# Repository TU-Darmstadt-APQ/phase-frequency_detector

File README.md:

Phase-Frequency Detector
=====================
This repository contains the [KiCad](https://www.kicad.org/) design files of a phase-frequency detector designed for application in optical phase-locked loops (OPLL). The detector compares a beat-note signal with a reference signal and creates an output signal proportional to the phase deviation of the beat-note from the reference. Optionally, the beat-note input can be equipped with a divider (default: 4) for a larger input-frequency range.  The module also comprises a fast analog proportional-derivative controller for high-bandwidth feedback. 

**Features**

- Input frequency range
  - 10 MHz to 1.3 GHz without divider
  - 500 MHz to 5.2 GHz with divider (HMC365)
- Input signal level: -10 dBm to +10 dBm
- Error signal output:
  - Bandwidth 4 MHz (2. order filter)
  - Output voltage ±1 V max. (high-Z)
- PD controller
  - Output voltage ±5 V max. (high-Z)
  - Level adjustable between 4% and 100% via frontpanel trim pot
  - Gain sign adjustable via frontpanel switch
  - Hardware adjustable corner-frequency (default: 0.8 MHz) and gain limit (default: 32 dB)

Assembly
---------------

The PCB is placed in a standard 19''-rack mount unit. Use the [switch breakout board](https://github.com/TU-Darmstadt-APQ/phase-frequency_detector_switch_breakout) for connecting the frontpanel switch of the PD controller. See `frontpanel/` folder for drawings and frontpanel artwork.

 Design Files
-------------------
The design files can be found on the [releases](../../releases) page and include the following resources:

- Schematics as a PDF
- Gerber files
- Pick & place position files
- Bill of materials as a CSV file and also as an interactive HTML version

The latest revision of those files can be found [here](../../releases/latest).

Related work
--------------------
T. Preuschoff, *Laser Technologies for Applications in Quantum Information Science*, Ph.D. thesis, TU Darmstadt, 2023, [https://tuprints.ulb.tu-darmstadt.de/23242/](https://tuprints.ulb.tu-darmstadt.de/23242/)

Requirements
----------------------
- Dual power supply
   - +15 V (0.35 A typ.)
   - \- 15 V (0.15 A typ.)
- 19-inch rack mount (e.g. [Fischer Elektronik BGT384](https://www.fischerelektronik.de/web_fischer/en_GB/cases/N05.1/19%22%20subracks/$catalogue/fischerData/PR/BGT384_180/search.xhtml))

License
-----------

This work is released under the CERN OHL v.1.2
See www.ohwr.org/licenses/cern-ohl/v1.2 or the included LICENSE file for more information.

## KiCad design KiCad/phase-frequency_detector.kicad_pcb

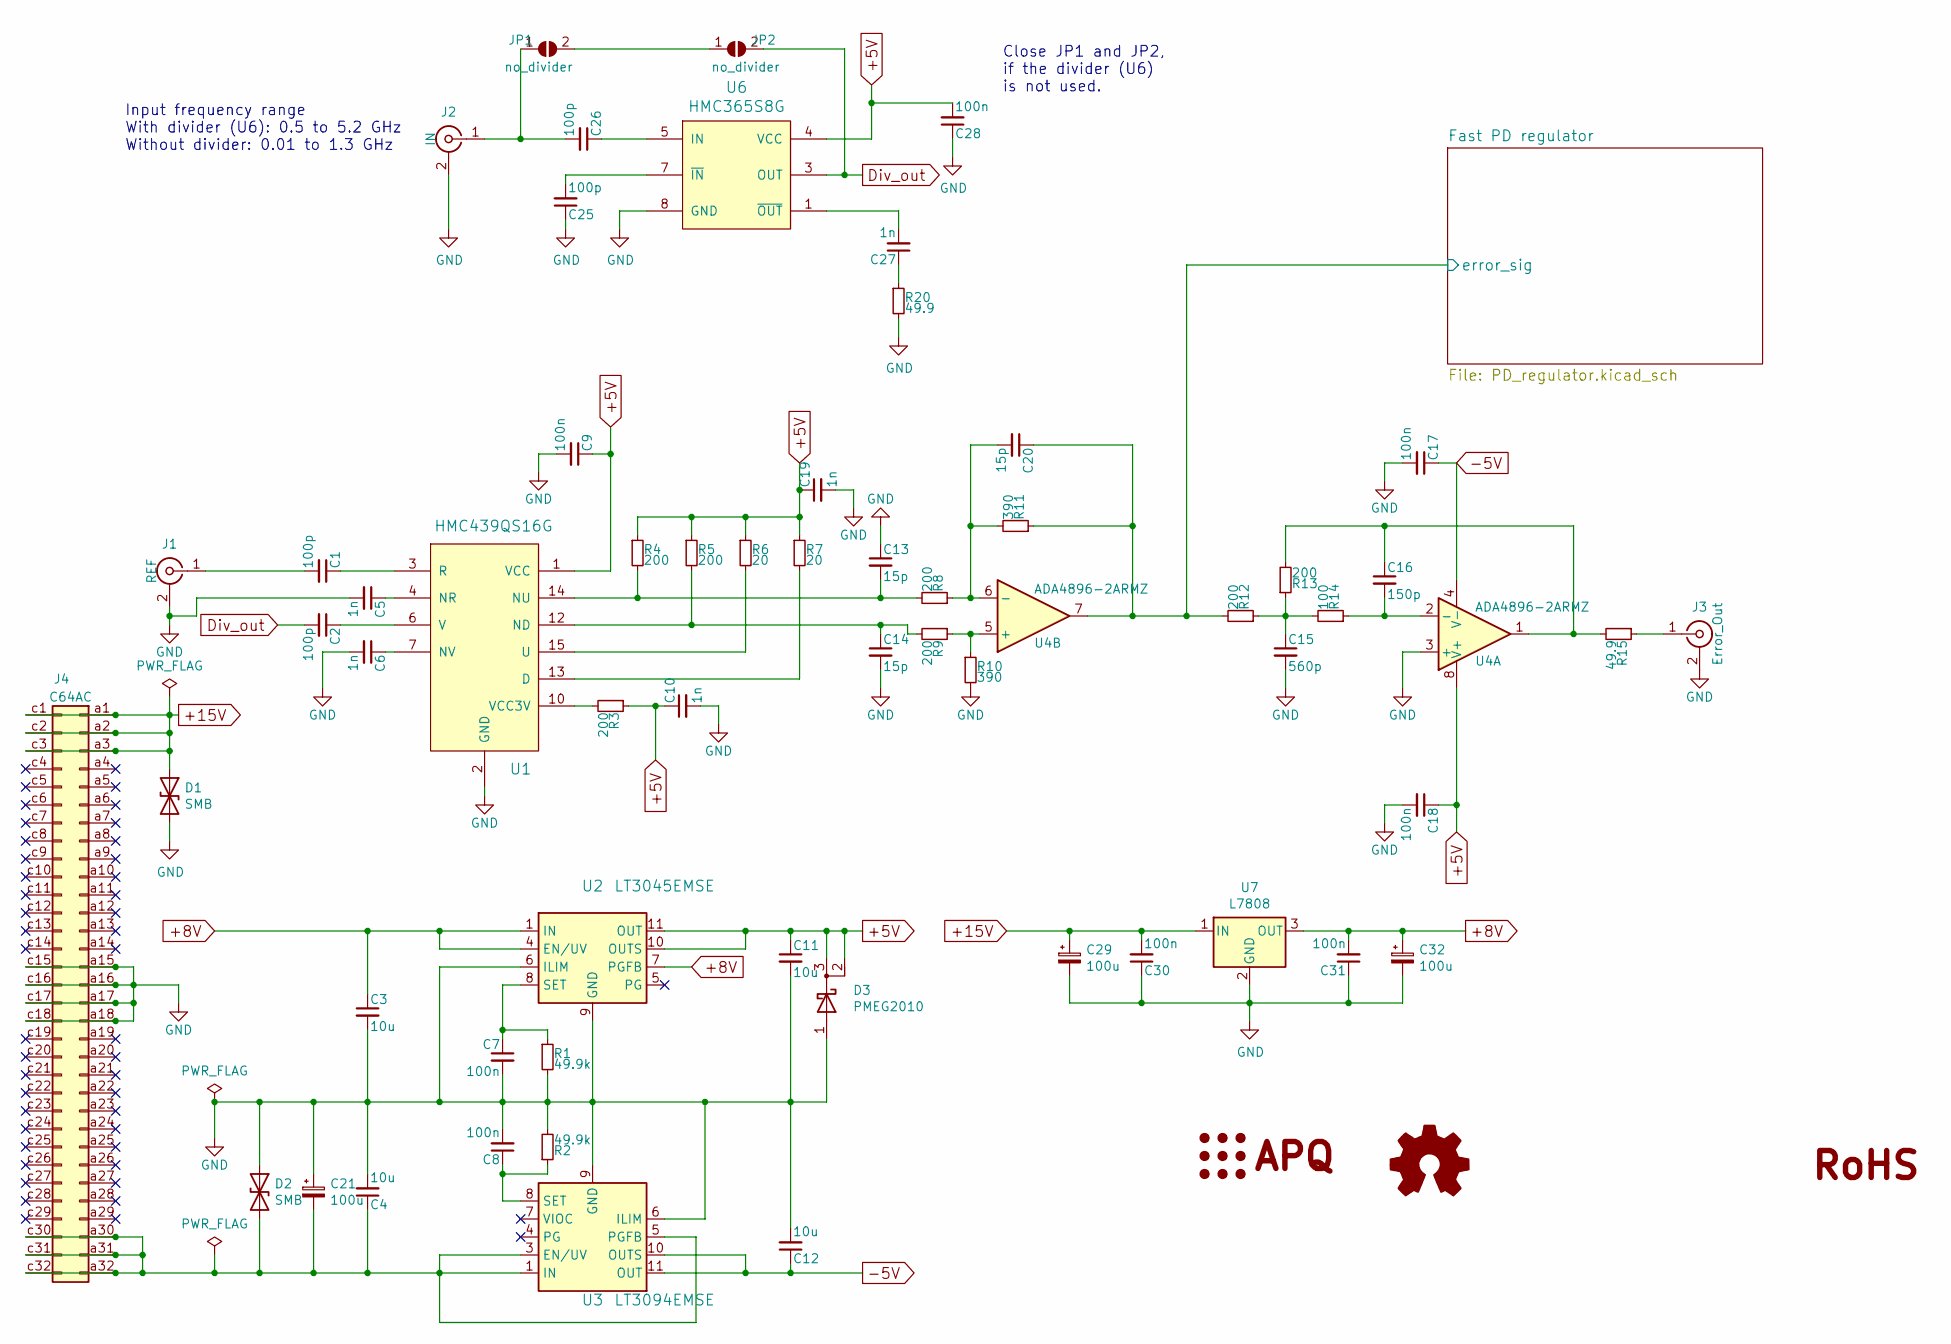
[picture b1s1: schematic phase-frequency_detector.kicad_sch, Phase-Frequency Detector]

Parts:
C1, C2, C25, C26: 100p; C_0603_1608Metric
C3, C4, C11, C12: 10u; C_1210_3225Metric
C5, C6, C10, C19, C27: 1n; C_0603_1608Metric
C7, C8: 100n; C_1206_3216Metric
C9, C17, C18, C28, C30, C31: 100n; C_0603_1608Metric
C13, C14, C20: 15p; C_0603_1608Metric
C15: 560p; C_0603_1608Metric
C16: 150p; C_0603_1608Metric
C21, C29, C32: 100u; CP_Radial_D5.0mm_P2.50mm
D1, D2: SMB; D_SMB
D3: PMEG2010; SOT-23
J1: REF; SMA_Amphenol_132289_EdgeMount
J2: IN; SMA_Amphenol_132289_EdgeMount
J3: Error_Out; BNC_Amphenol_B6252HB-NPP3G-50_Horizontal
J4: C64AC; DIN41612_C_2x32_Male_Horizontal_THT
JP1, JP2: no_divider; SolderJumper-2_P1.3mm_Open_RoundedPad1.0x1.5mm
LOGO1: Logo_APQ; APQ-Logo
LOGO2: Logo_Open_Hardware_Small; OSHW-Logo_5.7x6mm_SilkScreen
LOGO3: Logo_ROHS; RoHS-Logo_6mm_SilkScreen
R1, R2: 49.9k; R_0603_1608Metric
R3, R4, R5, R8, R9, R12, R13: 200; R_0603_1608Metric
R6, R7: 20; R_0603_1608Metric
R10, R11: 390; R_0603_1608Metric
R14: 100; R_0603_1608Metric
R15: 49.9; R_1210_3225Metric
R20: 49.9; R_0603_1608Metric
U1: HMC439QS16G; QSOP-16_3.9x4.9mm_P0.635mm_EP_2.3mmx1.75mm_DNF
U2: LT3045EMSE; MSOP-12-1EP_3x4mm_P0.65mm_EP1.65x2.85mm
U3: LT3094EMSE; MSOP-12-1EP_3x4mm_P0.65mm_EP1.65x2.85mm
U4: ADA4896-2ARMZ; MSOP-8_3x3mm_P0.65mm_mod
U6: HMC365S8G; SOIC-8-1EP_3.9x4.9mm_P1.27mm_EP2.41x3.81mm
U7: L7808; TO-220-3_Vertical

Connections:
+5V: C9.1, C10.1, C11.1, C18.1, C19.1, C28.2, D3.2 (K), D3.3 (K), R3.1, R4.1, R5.1, R6.1, R7.1, U1.1 (VCC), U2.10 (OUTS), U2.11 (OUT), U2.12 (OUT), U4.8 (V+), U6.4 (VCC); also elsewhere on the board
+8V: C3.1, C31.2, C32.1, U2.1 (IN), U2.2 (IN), U2.3 (IN), U2.4 (EN/UV), U2.7 (PGFB), U7.3 (OUT)
+15V: C29.1, C30.2, D1.1 (A1), J4.a1, J4.a2, J4.a3, J4.c1, J4.c2, J4.c3, U7.1 (IN)
-5V: C12.1, C17.1, U3.10 (OUTS), U3.11 (OUT), U3.12 (OUT), U4.4 (V-); also elsewhere on the board
/Fast PD regulator/error_sig: C20.1, R11.1, R12.2, U4.7; also elsewhere on the board
Div_out: C2.2, JP2.2 (B), U6.3 (OUT)
GND: C3.2, C4.2, C5.2, C6.2, C7.2, C8.2, C9.2, C10.2, C11.2, C12.2, C13.1, C14.2, C15.2, C17.2, C18.2, C19.2, C21.1, C25.1, C28.1, C29.2, C30.1, C31.1, C32.2, D1.2 (A2), D2.1 (A1), D3.1 (A), J1.2 (Ext), J2.2 (Ext), J3.2 (Ext), J4.a15, J4.a16, J4.a17, J4.a18, J4.c15, J4.c16, J4.c17, J4.c18, R1.2, R2.2, R10.2, R20.2, U1.2 (GND), U1.5 (GND), U1.8 (GND), U1.9 (GND), U1.11 (GND), U1.16 (GND), U1.17 (GND), U2.6 (ILIM), U2.9 (GND), U2.13 (GND), U3.6 (ILIM), U3.9 (GND), U4.3 (+), U6.8 (GND), U6.9 (GND), U7.2 (GND); also elsewhere on the board
unnamed: C15.1, R12.1, R13.1, R14.2
unnamed: C16.1, R13.2, R15.2, U4.1
unnamed: C27.1, R20.1
unnamed: C4.1, C21.2, D2.2 (A2), J4.a30, J4.a31, J4.a32, J4.c30, J4.c31, J4.c32, U3.1 (IN), U3.2 (IN), U3.3 (EN/UV), U3.5 (PGFB), U3.13 (IN)
unnamed: C1.2, J1.1 (In)
unnamed: C26.2, J2.1 (In), JP1.1 (A)
unnamed: J3.1 (In), R15.1
unnamed: JP1.2 (B), JP2.1 (A)
unnamed: R7.2, U1.13 (D)
unnamed: C14.1, R5.2, R9.2, U1.12 (ND)
unnamed: C5.1, U1.4 (NR)
unnamed: C13.2, R4.2, R8.2, U1.14 (NU)
unnamed: C6.1, U1.7 (NV)
unnamed: C1.1, U1.3 (R)
unnamed: R6.2, U1.15 (U)
unnamed: C2.1, U1.6 (V)
unnamed: R3.2, U1.10 (VCC3V)
unnamed: C7.1, R1.1, U2.8 (SET)
unnamed: C8.1, R2.1, U3.8 (SET)
unnamed: C16.2, R14.1, U4.2 (-)
unnamed: R9.1, R10.1, U4.5 (+)
unnamed: C20.2, R8.1, R11.2, U4.6 (-)
unnamed: C26.1, U6.5 (IN)
unnamed: C25.2, U6.7 (~IN)
unnamed: C27.2, U6.1 (~OUT)

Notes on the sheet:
Input frequency range With divider (U6): 0.5 to 5.2 GHz Without divider: 0.01 to 1.3 GHz
Close JP1 and JP2, if the divider (U6) is not used.

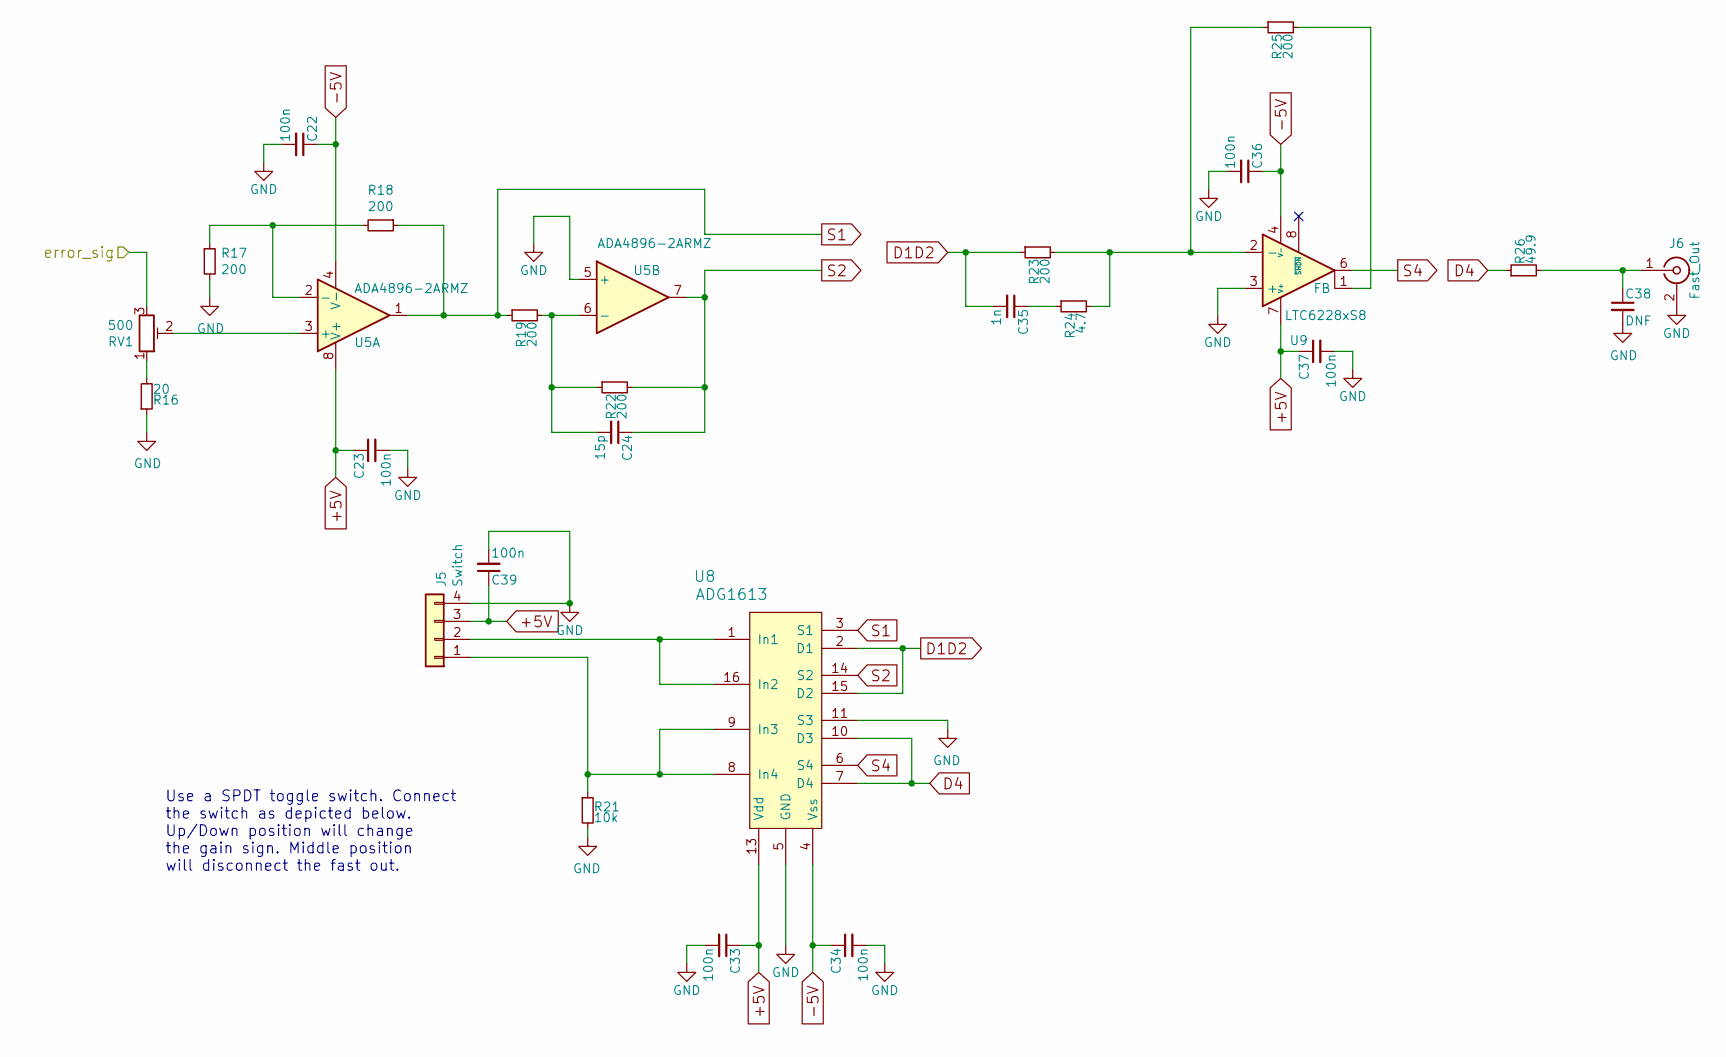
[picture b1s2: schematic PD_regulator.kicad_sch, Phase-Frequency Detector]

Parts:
C22, C23, C33, C34, C36, C37, C39: 100n; C_0603_1608Metric
C24: 15p; C_0603_1608Metric
C35: 1n; C_0603_1608Metric
C38: DNF; C_0603_1608Metric
J5: Switch; JST_PH_B4B-PH-K_1x04_P2.00mm_Vertical
J6: Fast_Out; BNC_Amphenol_B6252HB-NPP3G-50_Horizontal
R16: 20; R_0603_1608Metric
R17, R18, R19, R22, R23, R25: 200; R_0603_1608Metric
R21: 10k; R_0603_1608Metric
R24: 4.7; R_0603_1608Metric
R26: 49.9; R_1210_3225Metric
RV1: 500; Potentiometer_Vishay_43_Horizontal
U5: ADA4896-2ARMZ; MSOP-8_3x3mm_P0.65mm_mod
U8: ADG1613; TSSOP-16_4.4x5mm_P0.65mm
U9: LTC6228xS8; SO-8_3.9x4.9mm_P1.27mm

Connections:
+5V: C23.1, C33.1, C37.1, C39.1, J5.3, U5.8 (V+), U8.13 (Vdd), U9.7 (V+); also elsewhere on the board
-5V: C22.1, C34.1, C36.1, U5.4 (V-), U8.4 (Vss), U9.4 (V-), U9.5 (V-); also elsewhere on the board
/Fast PD regulator/error_sig: RV1.3; also elsewhere on the board
D1D2: C35.2, R23.1, U8.2 (D1), U8.15 (D2)
D4: R26.1, U8.7 (D4), U8.10 (D3)
GND: C22.2, C23.2, C33.2, C34.2, C36.2, C37.2, C38.2, C39.2, J5.4, J6.2 (Ext), R16.1, R17.2, R21.2, U5.5 (+), U8.5 (GND), U8.11 (S3), U9.3 (+); also elsewhere on the board
unnamed: C35.1, R24.1
unnamed: J5.1, R21.1, U8.8 (In4), U8.9 (In3)
unnamed: J5.2, U8.1 (In1), U8.16 (In2)
unnamed: C38.1, J6.1 (In), R26.2
unnamed: R16.2, RV1.1
unnamed: RV1.2, U5.3 (+)
unnamed: R17.1, R18.2, U5.2 (-)
unnamed: C24.2, R19.2, R22.1, U5.6 (-)
unnamed: R23.2, R24.2, R25.1, U9.2 (-)
unnamed: R25.2, U9.1 (FB)
S1: R18.1, R19.1, U5.1, U8.3 (S1)
S2: C24.1, R22.2, U5.7, U8.14 (S2)
S4: U8.6 (S4), U9.6

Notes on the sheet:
Use a SPDT toggle switch. Connect the switch as depicted below. Up/Down position will change the gain sign. Middle position will disconnect the fast out.

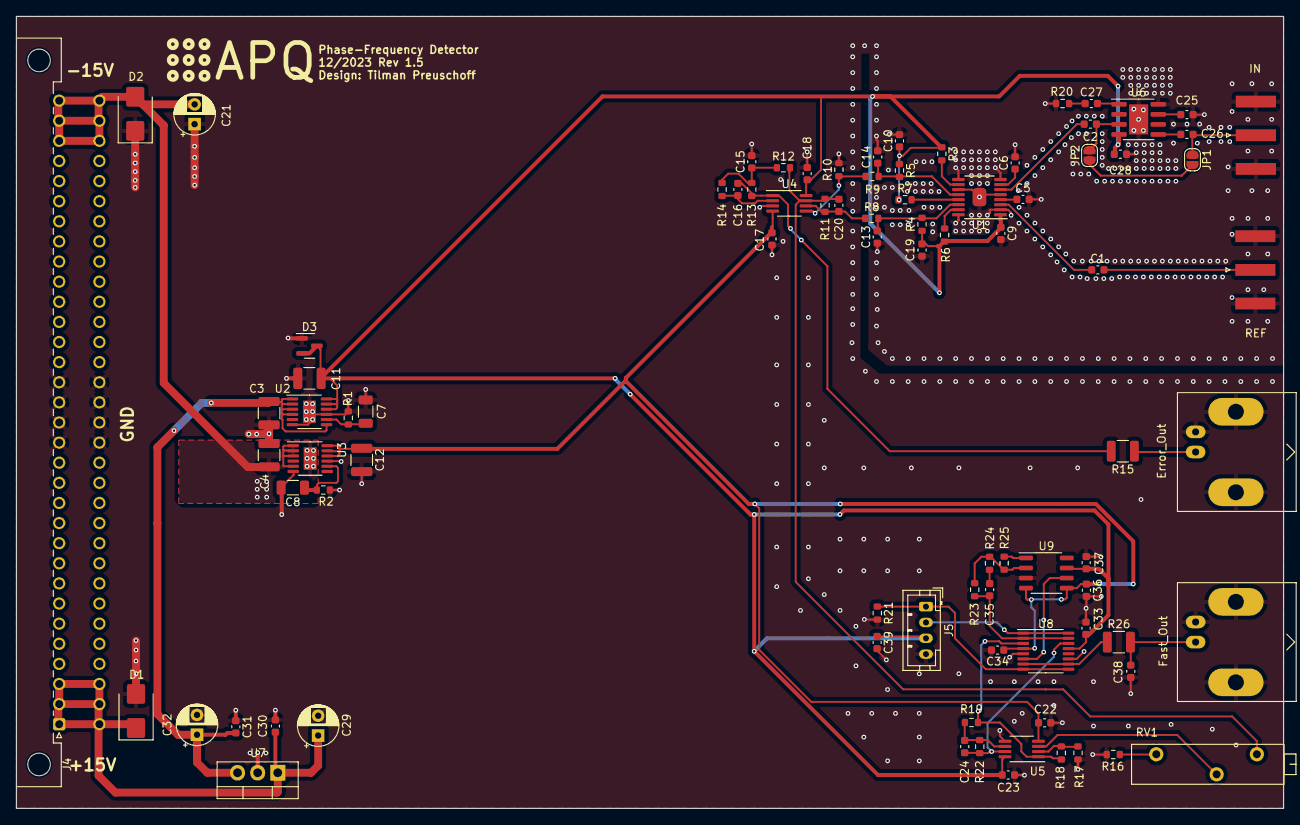
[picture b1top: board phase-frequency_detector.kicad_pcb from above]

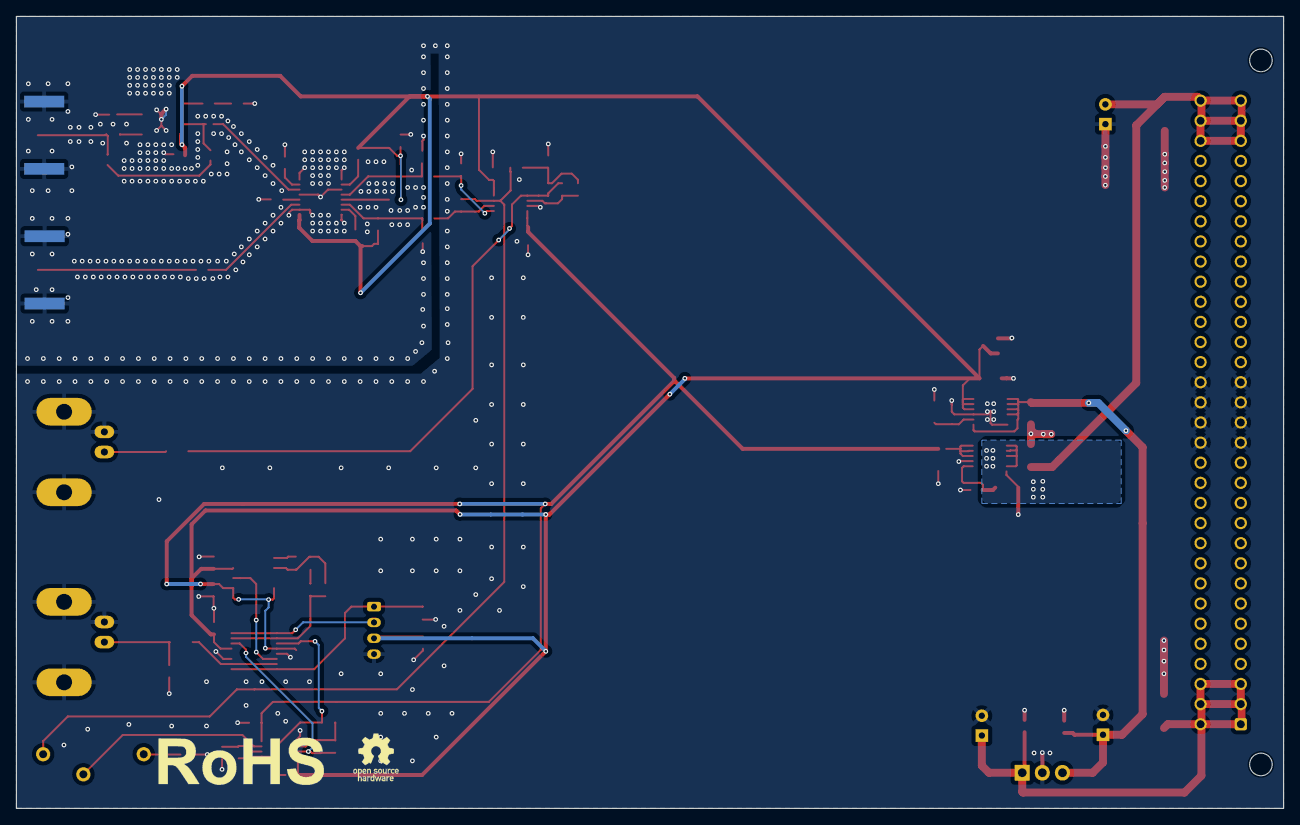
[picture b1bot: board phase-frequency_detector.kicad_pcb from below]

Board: 2 copper layers, 160.0 x 100.0 mm, 89 parts (2 on the bottom side), 47 nets.

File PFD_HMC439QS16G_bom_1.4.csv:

Component,Quantity Per PCB,References,Value,MFN,PN,Description,Footprint,Sheetpath
1,4,C13-C14  C20  C24,15p,Vishay / Vitramon,VJ0603A150JXBAC,"Unpolarized capacitor, small symbol",C_0603_1608Metric,/
2,4,C1-C2  C25-C26,100p,TDK,CGJ3E2C0G2A101J080AA,"Unpolarized capacitor, small symbol",C_0603_1608Metric,/
3,1,C16,150p,Vishay / Vitramon,VJ0603A151JXBAC,"Unpolarized capacitor, small symbol",C_0603_1608Metric,/
4,1,C15,560p,Vishay / Vitramon,VJ0603A561JXAAC,"Unpolarized capacitor, small symbol",C_0603_1608Metric,/
5,6,C5-C6  C10  C19  C27  C35,1n,KEMET,C0603X102K4RACAUTO,"Unpolarized capacitor, small symbol",C_0603_1608Metric,/
6,13,C9  C17-C18  C22-C23  C28  C30-C31  C33-C34  C36-C37  C39,100n,KEMET,C0603C104K5RAC3121,"Unpolarized capacitor, small symbol",C_0603_1608Metric,/
7,2,C7-C8,100n,Murata-Electronics,GRM3195C2A104JA01D,"Unpolarized capacitor, small symbol",C_1206_3216Metric,/
8,4,C3-C4  C11-C12,10u,TDK,C3225X7R2A106K250AC,"Unpolarized capacitor, small symbol",C_1210_3225Metric,/
9,3,C21  C29  C32,100u,Panasonic,ECA-1AM101I,"Polarized capacitor, small symbol",CP_Radial_D5.0mm_P2.50mm,/
10,1,D3,PMEG2010,Nexperia,"PMEG2010AET,215","Schottky diode, cathode on pins 2 and 3",SOT-23,/
11,2,D1-D2,SMB,Bourns,SMBJ40CA-QH,Bidirectional transient-voltage-suppression diode,D_SMB,/
12,1,J4,C64AC,Harting,09221326921222,"DIN41612 connector, double row (AC), 02x32, script generated (kicad-library-utils/schlib/autogen/connector/)",DIN41612_C_2x32_Male_Horizontal_THT,/
13,1,J3,Error_Out,Linx Technologies,CONBNC002,"coaxial connector (BNC, SMA, SMB, SMC, Cinch/RCA, LEMO, ...)",BNC_Amphenol_B6252HB-NPP3G-50_Horizontal,/
14,1,J6,Fast_Out,Linx Technologies,CONREVSMA006.062-G,"coaxial connector (BNC, SMA, SMB, SMC, Cinch/RCA, LEMO, ...)",BNC_Amphenol_B6252HB-NPP3G-50_Horizontal,/Fast PD regulator/
15,2,J1-J2,REF,Linx Technologies,CONREVSMA006.062-G,"coaxial connector (BNC, SMA, SMB, SMC, Cinch/RCA, LEMO, ...)",SMA_Amphenol_132289_EdgeMount,/
16,1,J5,Switch,JST,B4B-PH-K-S,"Generic connector, single row, 01x04, script generated (kicad-library-utils/schlib/autogen/connector/)",JST_PH_B4B-PH-K_1x04_P2.00mm_Vertical,/Fast PD regulator/
17,1,R24,4.7,ROHM Semiconductor,SDR03EZPF4R70,"Resistor, small symbol",R_0603_1608Metric,/Fast PD regulator/
18,3,R6-R7  R16,20,Yageo,AC0603FR-0720RL,"Resistor, small symbol",R_0603_1608Metric,/
19,2,R15  R26,49.9,Vishay / Dale,CRCW121049R9FKEA,"Resistor, small symbol",R_1210_3225Metric,/
20,1,R20,49.9,Panasonic,ERJ-UP3F49R9V,"Resistor, small symbol",R_0603_1608Metric,/
21,1,R14,100,Yageo,RC0603FR-13100RL,"Resistor, small symbol",R_0603_1608Metric,/
22,13,R3-R5  R8-R9  R12-R13  R17-R19  R22-R23  R25,200,Yageo,RC0603FR-13200RL,"Resistor, small symbol",R_0603_1608Metric,/
23,2,R10-R11,390,Yageo,RC0603FR-13390RL,"Resistor, small symbol",R_0603_1608Metric,/
24,1,R21,10k,Panasonic,ERJ-3GEYJ103V,"Resistor, small symbol",R_0603_1608Metric,/Fast PD regulator/
25,2,R1-R2,49.9k,Panasonic,ERJ-UP3F4992V,"Resistor, small symbol",R_0603_1608Metric,/
26,1,RV1,500,Vishay / Spectrol,M43P501KB40,Trim-potentiometer,Potentiometer_Vishay_43_Horizontal,/Fast PD regulator/
27,2,U4-U5,ADA4896-2ARMZ,Analog Devices,ADA4896-2ARMZ,"1 nV/√Hz, Low Power,Rail-to-Rail Output Amplifier",MSOP-8_3x3mm_P0.65mm_mod,/
28,1,U8,ADG1613,Analog Devices,ADG1613BRUZ,,TSSOP-16_4.4x5mm_P0.65mm,/Fast PD regulator/
29,1,U7,L7808,STMicroelectronics,L7808ABV-DG,"Positive 1.5A 35V Linear Regulator, Fixed Output 8V, TO-220/TO-263/TO-252",TO-220-3_Vertical,/
30,1,U2,LT3045EMSE,Analog Devices,LT3045EMSE#PBF,"20V, 500mA, Ultralow Noise, Ultrahigh PSRR Linear Regulator, MSOP Package",MSOP-12-1EP_3x4mm_P0.65mm_EP1.65x2.85mm,/
31,1,U3,LT3094EMSE,Analog Devices,LT3094EMSE#PBF,"–20V, 500mA, Ultralow Noise, Ultrahigh PSRR Negative Linear Regulator, MSOP Package",MSOP-12-1EP_3x4mm_P0.65mm_EP1.65x2.85mm,/
32,1,U9,LTC6228xS8,Analog Devices,LTC6228IS8#PBF,"Low Distortion Rail-to-Rail Output Op Amp with Shutdown, SO-8",SO-8_3.9x4.9mm_P1.27mm,/Fast PD regulator/





Component Groups:,36
Component Count:,86
Fitted Components:,81
Number of PCBs:,1
Total components:,81
Schematic Version:,1.4
Schematic Date:,2022-01-25
PCB Variant:,default
BoM Date:,22.03.2023 21:40:04
Schematic Source:,PFD_HMC439QS16G.kicad_sch
KiCad Version:,Eeschema (6.0.7)

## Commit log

2020-11-23 Rev 1.1
2020-12-04 Reverse Trimpot. Update gerber files
2021-03-18 Rev. 1.2
    -Divide input signal by 4 using HMC365
    -Change board layout to standard eurocard
    -Minor changes to 'Fast Out': Optional AC-coupling, optional gain
2021-03-19 Add gain of 2 and increase bandwidth at U4B
2021-03-19 Add footprint position files
2021-03-21 Update gerber files
2021-08-22 Remove HMC365 frequency divider
2021-08-23 Update revision label on PCB
2021-12-02 Update error signal gains and fix copper pour at LT3094
2021-12-02 Add LM7908 and TVS diodes for line protection
2022-01-17 First draft: fast PD regulator
2022-01-18 Fast PD second draft
2022-01-18 Spice simulations
2022-01-18 Add fast PD regulator
2022-01-18 Add drawing and comment for switch connection
2022-01-24 Add 'no divider' option and clamping diode / Update to KiCad 6
2022-01-25 Fix HMC365 and ADG1413 symbols. Update gerber files.
2022-01-25 Remove additional KiCad 5 gerber files
2022-01-27 Remove KiCad 5 files and ignore backup files
2022-01-27 Update BOM / fix some fottprints
2022-06-09 Updated BOM with new parts
2022-06-13 Update BOM.ini. Generate BOM.
2023-03-22 Update BOM
2023-03-22 Rename project files
2023-03-22 Add comments and fix custom footprint lib.
2023-03-22 Remove solder paste from DNF footprints.
2023-03-22 Add 3D models
2023-06-16 Create frontpanel design
2023-06-16 Add assembly instructions
2023-06-16 Replace ADG1613 with ADG1413 due to better availability
2023-06-16 Remove obsolete gerber files
2023-06-23 Create switch breakout board
2023-06-23 Replaced swtich_breakout with submodule
2023-06-23 Update frontpanel
2023-06-23 Correct PN for Harting and BNC connectors
2023-06-28 Update frontpanel drawing
2023-06-28 Add frontpanel print
2023-06-30 Add case PN
2023-06-30 Add frontpanel manufacturing information
2023-08-08 Update assembly model
2023-10-14 Reworked frontpanel artwork
2023-11-02 Add README and LICENSE
2023-11-02 Fix ADG1413/1613 symbol
2023-11-03 Updated to KiCad 7 Added CI pipeline Fixed trailing whitespaces of MFN and PN labels Fixed ERC/DRC errors
2023-11-03 Do not checkout submodules. They are not required
2023-11-05 Fixed logos on schematic
2023-11-05 cleanup
2023-11-06 Bump switch_breakout from `e1719e6` to `3b2b977`
    Bumps [switch_breakout](https://github.com/TU-Darmstadt-APQ/phase-frequency_detector_switch_breakout) from `e1719e6` to `3b2b977`.
    - [Release notes](https://github.com/TU-Darmstadt-APQ/phase-frequency_detector_switch_breakout/releases)
    - [Commits](https://github.com/TU-Darmstadt-APQ/phase-frequency_detector_switch_breakout/compare/e1719e65053c7a6c27b33b2e67abfd7177f710e9...3b2b97732aaf6d5b28b69c52752f8d6397ca57bb)
    ---
    updated-dependencies:
    - dependency-name: switch_breakout
2023-11-07 Update LT3045/LT3094 symbols
2023-11-08 Update .gitmodules
    Changed submodule path to a relative path
2023-11-08 Add model for Fischer KN1
2023-12-14 [gha] Bump actions/download-artifact from 3 to 4
    Bumps [actions/download-artifact](https://github.com/actions/download-artifact) from 3 to 4.
    - [Release notes](https://github.com/actions/download-artifact/releases)
    - [Commits](https://github.com/actions/download-artifact/compare/v3...v4)
    ---
    updated-dependencies:
    - dependency-name: actions/download-artifact
2023-12-14 [gha] Bump actions/upload-artifact from 3 to 4
    Bumps [actions/upload-artifact](https://github.com/actions/upload-artifact) from 3 to 4.
    - [Release notes](https://github.com/actions/upload-artifact/releases)
    - [Commits](https://github.com/actions/upload-artifact/compare/v3...v4)
    ---
    updated-dependencies:
    - dependency-name: actions/upload-artifact
2023-12-15 Move BNC connectors to be flush with edge-mount SMA connectors
2023-12-15 Update pcb image
2023-12-17 Updated to actions/download-artifact@v4
2023-12-17 Fixed submodule URL
2023-12-17 Change switch breakout to submodule
2023-12-17 Bump version of switch breakout
2024-02-26 Fix artifact upload
2025-08-07 Bump switch_breakout from `e3cf733` to `a8cd211`
    Bumps [switch_breakout](https://github.com/TU-Darmstadt-APQ/phase-frequency_detector_switch_breakout) from `e3cf733` to `a8cd211`.
    - [Release notes](https://github.com/TU-Darmstadt-APQ/phase-frequency_detector_switch_breakout/releases)
    - [Commits](https://github.com/TU-Darmstadt-APQ/phase-frequency_detector_switch_breakout/compare/e3cf733fa28ee9e9b3a202e3d92bd92609e3e065...a8cd21180e583919de076987f8dedbac1473b8f9)
    ---
    updated-dependencies:
    - dependency-name: switch_breakout
2025-08-12 Bump switch_breakout from `a8cd211` to `b494cff`
    Bumps [switch_breakout](https://github.com/TU-Darmstadt-APQ/phase-frequency_detector_switch_breakout) from `a8cd211` to `b494cff`.
    - [Release notes](https://github.com/TU-Darmstadt-APQ/phase-frequency_detector_switch_breakout/releases)
    - [Commits](https://github.com/TU-Darmstadt-APQ/phase-frequency_detector_switch_breakout/compare/a8cd21180e583919de076987f8dedbac1473b8f9...b494cffa423c276e74c238047f78d964488781c3)
    ---
    updated-dependencies:
    - dependency-name: switch_breakout
2025-10-28 Bump switch_breakout from `b494cff` to `1e6b422`
    Bumps [switch_breakout](https://github.com/TU-Darmstadt-APQ/phase-frequency_detector_switch_breakout) from `b494cff` to `1e6b422`.
    - [Release notes](https://github.com/TU-Darmstadt-APQ/phase-frequency_detector_switch_breakout/releases)
    - [Commits](https://github.com/TU-Darmstadt-APQ/phase-frequency_detector_switch_breakout/compare/b494cffa423c276e74c238047f78d964488781c3...1e6b422beb8fc347eb67b56b1d1218f6f97b37d8)
    ---
    updated-dependencies:
    - dependency-name: switch_breakout
2025-11-21 Bump switch_breakout from `1e6b422` to `9c009a8`
    Bumps [switch_breakout](https://github.com/TU-Darmstadt-APQ/phase-frequency_detector_switch_breakout) from `1e6b422` to `9c009a8`.
    - [Release notes](https://github.com/TU-Darmstadt-APQ/phase-frequency_detector_switch_breakout/releases)
    - [Commits](https://github.com/TU-Darmstadt-APQ/phase-frequency_detector_switch_breakout/compare/1e6b422beb8fc347eb67b56b1d1218f6f97b37d8...9c009a8bfb0dfe8e3a57551d8958ebf1a7e61672)
    ---
    updated-dependencies:
    - dependency-name: switch_breakout
2025-12-16 Bump switch_breakout from `9c009a8` to `ca648f9`
    Bumps [switch_breakout](https://github.com/TU-Darmstadt-APQ/phase-frequency_detector_switch_breakout) from `9c009a8` to `ca648f9`.
    - [Release notes](https://github.com/TU-Darmstadt-APQ/phase-frequency_detector_switch_breakout/releases)
    - [Commits](https://github.com/TU-Darmstadt-APQ/phase-frequency_detector_switch_breakout/compare/9c009a8bfb0dfe8e3a57551d8958ebf1a7e61672...ca648f90b1d18c7b812771cf5f24680b2d2a52d9)
    ---
    updated-dependencies:
    - dependency-name: switch_breakout
2026-03-02 Bump switch_breakout from `ca648f9` to `b1cbbb5`
    Bumps [switch_breakout](https://github.com/TU-Darmstadt-APQ/phase-frequency_detector_switch_breakout) from `ca648f9` to `b1cbbb5`.
    - [Release notes](https://github.com/TU-Darmstadt-APQ/phase-frequency_detector_switch_breakout/releases)
    - [Commits](https://github.com/TU-Darmstadt-APQ/phase-frequency_detector_switch_breakout/compare/ca648f90b1d18c7b812771cf5f24680b2d2a52d9...b1cbbb50e56310144436e7d2218c8a261a7624ba)
    ---
    updated-dependencies:
    - dependency-name: switch_breakout
2026-04-29 [gha] Bump actions/upload-artifact from 4 to 7
    Bumps [actions/upload-artifact](https://github.com/actions/upload-artifact) from 4 to 7.
    - [Release notes](https://github.com/actions/upload-artifact/releases)
    - [Commits](https://github.com/actions/upload-artifact/compare/v4...v7)
    ---
    updated-dependencies:
    - dependency-name: actions/upload-artifact
2026-04-29 [gha] Bump actions/checkout from 4 to 6
    Bumps [actions/checkout](https://github.com/actions/checkout) from 4 to 6.
    - [Release notes](https://github.com/actions/checkout/releases)
    - [Changelog](https://github.com/actions/checkout/blob/main/CHANGELOG.md)
    - [Commits](https://github.com/actions/checkout/compare/v4...v6)
    ---
    updated-dependencies:
2026-04-29 [gha] Bump actions/download-artifact from 4 to 8
    Bumps [actions/download-artifact](https://github.com/actions/download-artifact) from 4 to 8.
    - [Release notes](https://github.com/actions/download-artifact/releases)
    - [Commits](https://github.com/actions/download-artifact/compare/v4...v8)
    ---
    updated-dependencies:
    - dependency-name: actions/download-artifact
2026-06-18 [gha] Bump actions/checkout from 6 to 7
    Bumps [actions/checkout](https://github.com/actions/checkout) from 6 to 7.
    - [Release notes](https://github.com/actions/checkout/releases)
    - [Changelog](https://github.com/actions/checkout/blob/main/CHANGELOG.md)
    - [Commits](https://github.com/actions/checkout/compare/v6...v7)
    ---
    updated-dependencies:
2026-06-19 Bump switch_breakout from `b1cbbb5` to `60bbcf6`
    Bumps [switch_breakout](https://github.com/TU-Darmstadt-APQ/phase-frequency_detector_switch_breakout) from `b1cbbb5` to `60bbcf6`.
    - [Release notes](https://github.com/TU-Darmstadt-APQ/phase-frequency_detector_switch_breakout/releases)
    - [Commits](https://github.com/TU-Darmstadt-APQ/phase-frequency_detector_switch_breakout/compare/b1cbbb50e56310144436e7d2218c8a261a7624ba...60bbcf69a6fc8c99bafb40f163c101590ebd77fb)
    ---
    updated-dependencies:
    - dependency-name: switch_breakout
